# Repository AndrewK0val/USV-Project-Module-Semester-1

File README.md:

# USV-Project-Module-Semester-1
In this module I learned the process of electronic device design by creating a custom PCB board which will connect to a BBC Microbit module.
This custom board expands the existing feature-set of the BBC microbit by adding Wi-Fi networking and Bluetooth support, an LCD screen,
eight servo motor connections, audio output, and serial communication.

Autodesk Eagle was used to create the schematic and board design.

This is the finished schematic design:

Shown below is the complete board design:

Once the two designs were complete, gerber files were generated in Eagle and sent to a PCB manufacturer.
Depicted below is the printed PCB board:

This is the current iteration of the enclusure design to house the interface device. I have an obsession for automodive body design therefore
I wanted to incorporate a sports-car aesthetic to the housing of my custom board.
I plan to drill two holes on each side for each circular insert section to route cables for the 12v power and audio jack.
The design was created in Blender (free and open-source 3d-graphics and visual effects software)

This design will be 3D-printed in two parts (the main body and the lid) on an Ender 3 Pro 3D printer.

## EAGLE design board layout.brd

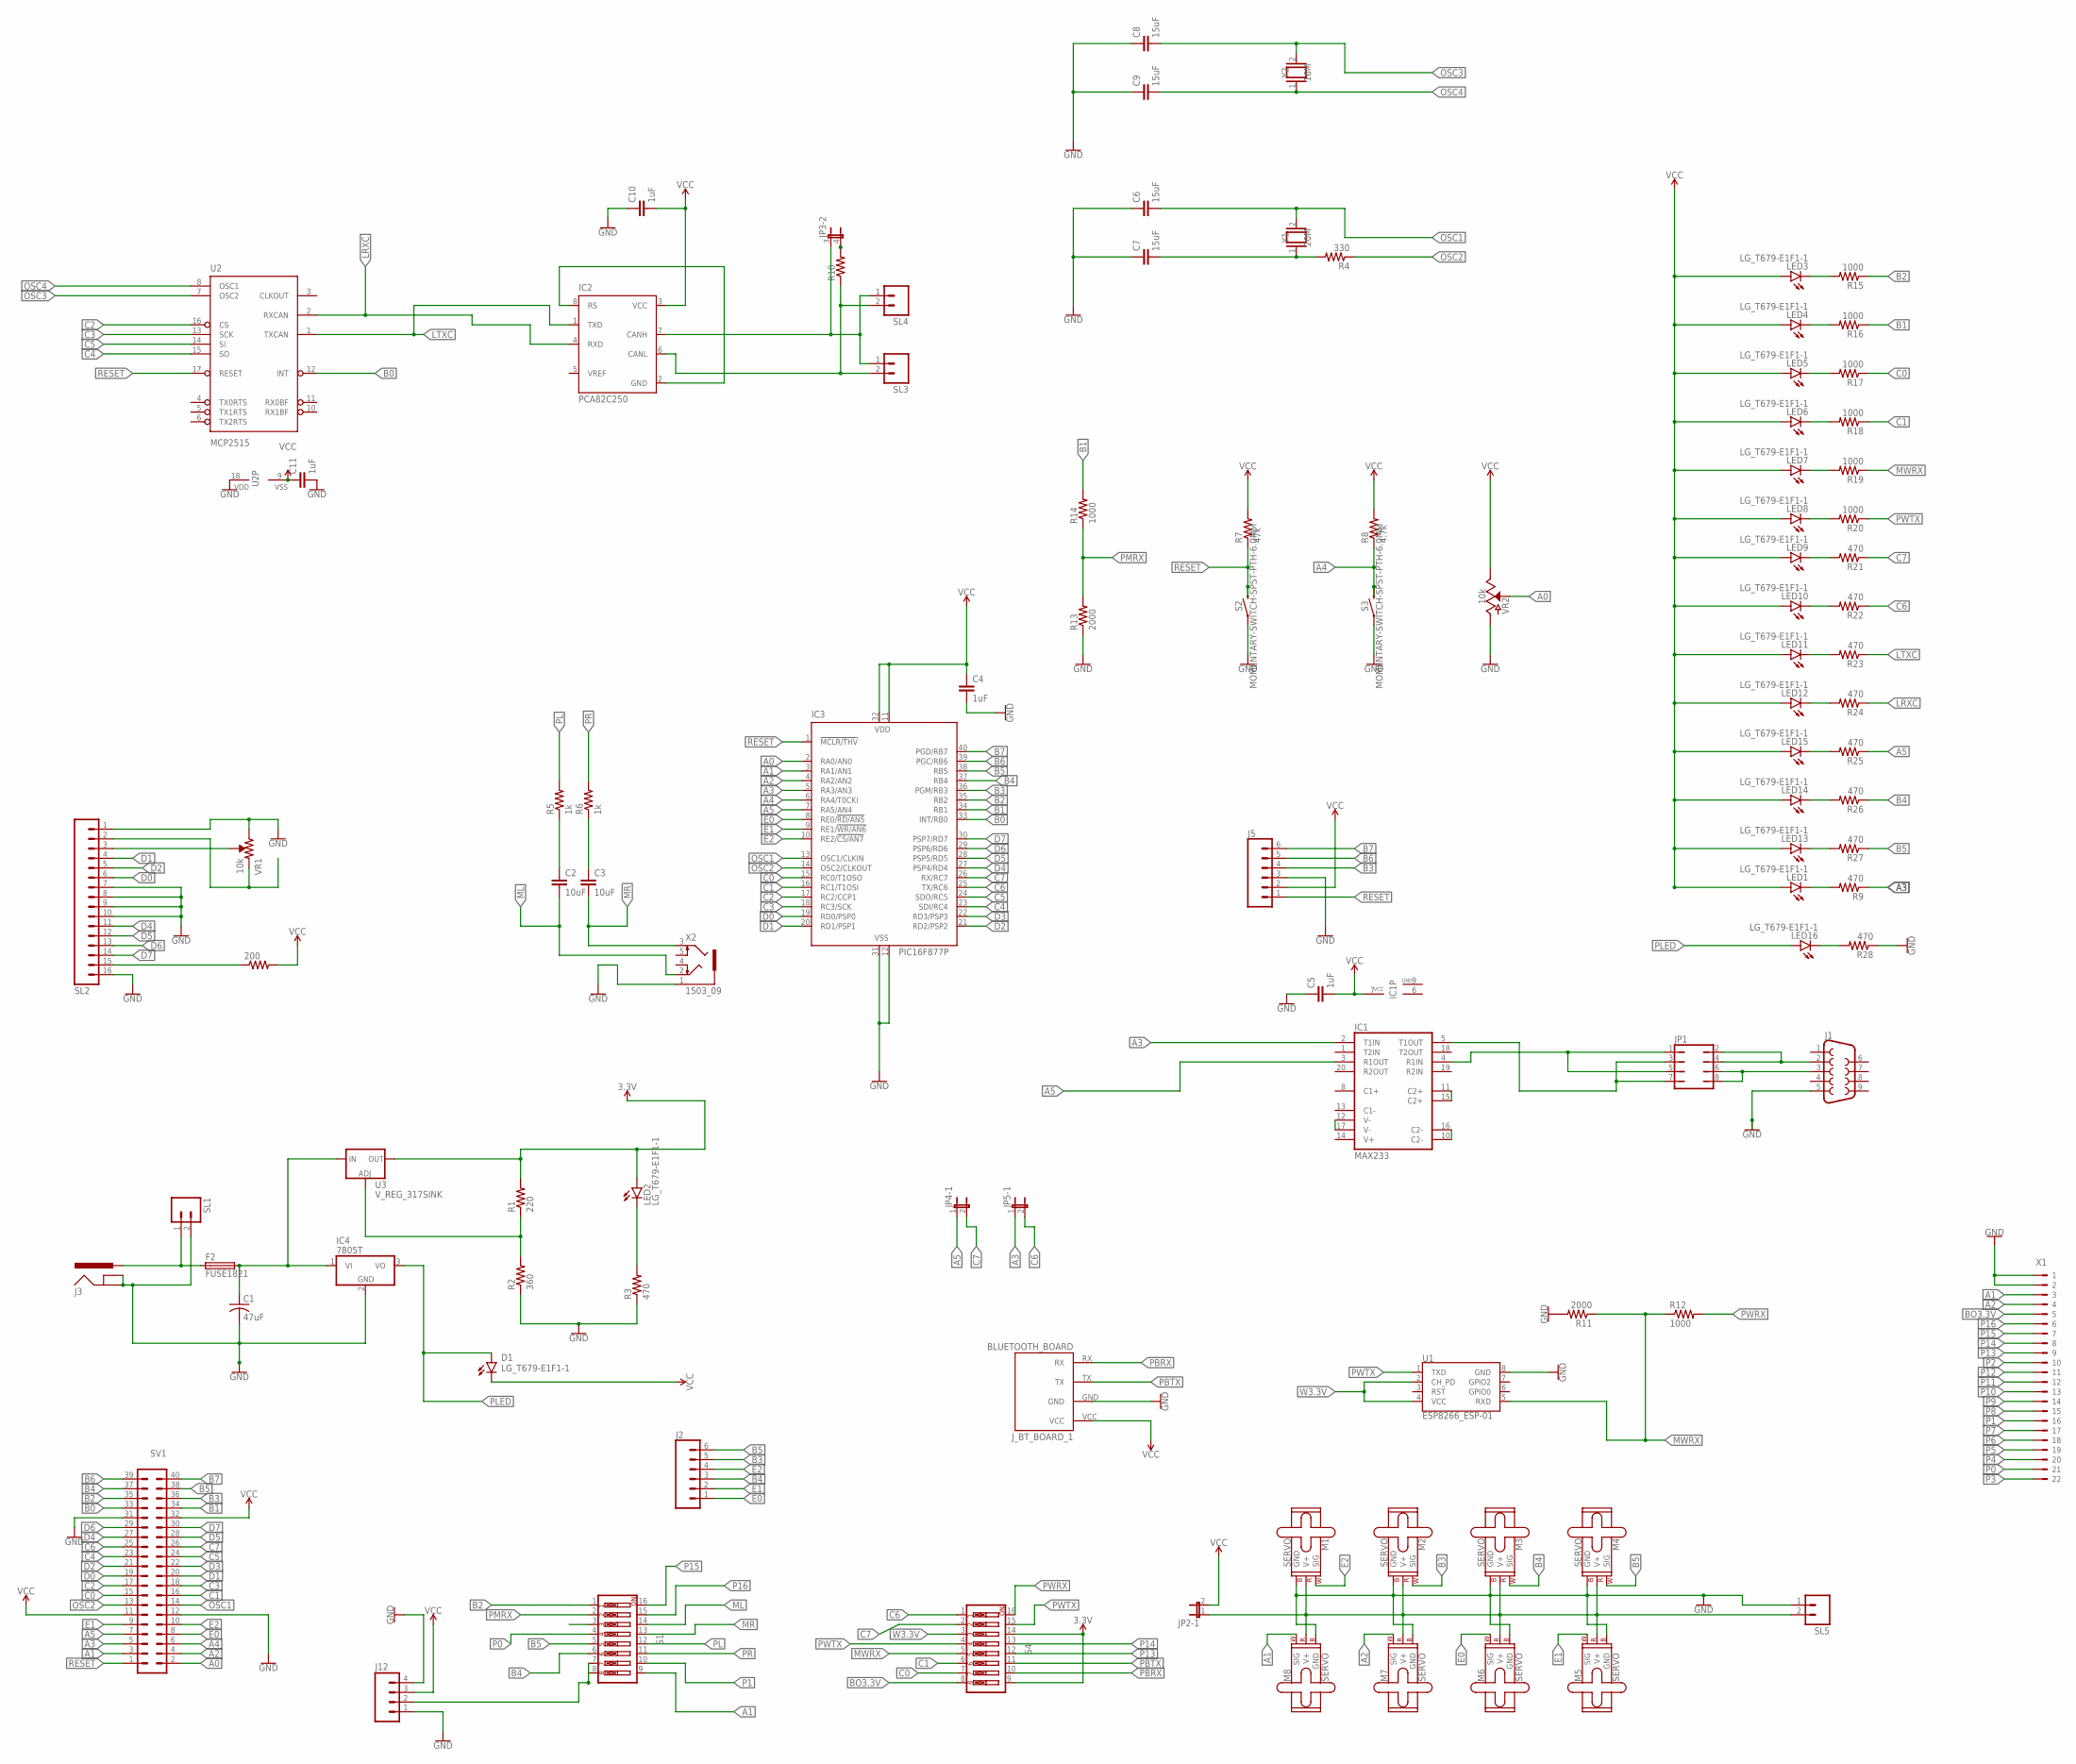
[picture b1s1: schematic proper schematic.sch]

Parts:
200: R-US_0204/5; 0204/5
C1: 47uF; C025-025X050
C2, C3: 10uF; C2.5-3
C4, C5, C10, C11: 1uF; C2.5-3
C6, C7, C8, C9: 15uF; C2.5-3
D1: LG_T679-E1F1-1; PLCC2
F2: FUSE1821; FUSE_HOLDER_MENTOR-1821
IC1: MAX233; DIL20
IC2: PCA82C250; DIL08
IC3: PIC16F877P; DIL40
IC4: 7805T; TO220H
J1: DB9FEMALE; DB9
J2, J5: CONN_062.5MM-6-90; 1X06_SCREW_TERMINAL_BLOCK
J3: POWER_JACK; POWER_JACK_PTH
J12: M04; 04P
JP1: JP4Q
JP2, JP3, JP4, JP5: JP2QE; JP2Q
J_BT_BOARD_1: BLUETOOTH_BOARD; BT_BOARD_FOOTPRINT
LED1, LED2, LED3, LED4, LED5, LED6, LED7, LED8, LED9, LED10, LED11, LED12, LED13, LED14, LED15, LED16: LG_T679-E1F1-1; PLCC2
M1, M2, M3, M4, M5, M6, M7, M8: SERVO; 1X03
R1: 220; 0204/5
R2: 360; 0204/5
R3, R9, R21, R22, R23, R24, R25, R26, R27, R28: 470; 0204/5
R4: 330; 0204/5
R5, R6: 1k; 0204/5
R7: 47k; 0204/5
R8: 4.7k; 0204/5
R10: R-US_0204/5; 0204/5
R11, R13: 2000; 0204/5
R12, R14, R15, R16, R17, R18, R19, R20: 1000; 0204/5
S1, S4: SW_DIP-8; EDG-08
S2, S3: MOMENTARY-SWITCH-SPST-PTH-6.0MM; TACTILE_SWITCH_PTH_6.0MM
SL1, SL3, SL4, SL5: M02; 02P
SL2: M16; 16P
SV1: MA20-2
U1: ESP8266_ESP-01
U2: MCP2515; DIP18
U3: V_REG_317SINK; TO220-ADJ
VR1: 10k; TRIMPOT-PTH-3386U
VR2: 10k; POT-PTH-ALPS
X1: 180G-22
X2: 1503_09
Y1: 20M; QS
Y2: 16M; QS

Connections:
3.3V: LED2.A, R1.2, S4.9, S4.14, U3.OUT
A0: IC3.2 (RA0/AN0), SV1.2, VR2.P$2 (S), VR2.P$3 (A)
A1: IC3.3 (RA1/AN1), M8.1 (SIG), S1.9, SV1.3, X1.3
A2: IC3.4 (RA2/AN2), M7.1 (SIG), SV1.4, X1.4
A3: IC1.2 (T1IN), IC3.5 (RA3/AN3), JP5.1, R9.1, SV1.5
A4: IC3.6 (RA4/T0CKI), R8.1, S3.3 (2), SV1.6
A5: IC1.3 (R1OUT), IC3.7 (RA5/AN4), JP4.1, R25.1, SV1.7
B0: IC3.33 (INT/RB0), SV1.33, U2.12 (INT)
B1: IC3.34 (RB1), R14.2, R16.1, SV1.34
B2: IC3.35 (RB2), R15.1, S1.1, SV1.35
B3: IC3.36 (PGM/RB3), J2.5, J5.4, M2.1 (SIG), SV1.36
B4: IC3.37 (RB4), J2.3, M3.1 (SIG), R26.1, S1.6, SV1.37
B5: IC3.38 (RB5), J2.6, M4.1 (SIG), R27.1, S1.5, SV1.38
B6: IC3.39 (PGC/RB6), J5.5, SV1.39
B7: IC3.40 (PGD/RB7), J5.6, SV1.40
BO3.3V: S4.8, X1.5
C0: IC3.15 (RC0/T1OSO), R17.1, S4.7, SV1.15
C1: IC3.16 (RC1/T1OSI), R18.1, S4.6, SV1.16
C2: IC3.17 (RC2/CCP1), SV1.17, U2.16 (CS)
C3: IC3.18 (RC3/SCK), SV1.18, U2.13 (SCK)
C4: IC3.23 (SDI/RC4), SV1.23, U2.15 (SO)
C5: IC3.24 (SDO/RC5), SV1.24, U2.14 (SI)
C6: IC3.25 (TX/RC6), JP5.2, R22.1, S4.1, SV1.25
C7: IC3.26 (RX/RC7), JP4.2, R21.1, S4.2, SV1.26
D0: IC3.19 (RD0/PSP0), SL2.6, SV1.19
D1: IC3.20 (RD1/PSP1), SL2.4, SV1.20
D2: IC3.21 (RD2/PSP2), SL2.5, SV1.21
D3: IC3.22 (RD3/PSP3), SV1.22
D4: IC3.27 (PSP4/RD4), SL2.11, SV1.27
D5: IC3.28 (PSP5/RD5), SL2.12, SV1.28
D6: IC3.29 (PSP6/RD6), SL2.13, SV1.29
D7: IC3.30 (PSP7/RD7), SL2.14, SV1.30
E0: IC3.8 (RE0/!RD/AN5), J2.1, M6.1 (SIG), SV1.8
E1: IC3.9 (RE1/!WR/AN6), J2.2, M5.1 (SIG), SV1.9
E2: IC3.10 (RE2/!CS/AN7), J2.4, M1.1 (SIG), SV1.10
GND: C1.2, C4.2, C5.1, C6.1, C7.1, C8.1, C9.1, C10.1, C11.2, IC1.6 (GND), IC1.9 (GND), IC3.12 (VSS), IC3.31 (VSS), IC4.2 (GND), J1.5, J3.GND, J3.GNDBREAK, J5.3, J12.1, J12.4, J_BT_BOARD_1.GND, M1.3 (GND), M2.3 (GND), M3.3 (GND), M4.3 (GND), M5.3 (GND), M6.3 (GND), M7.3 (GND), M8.3 (GND), R2.1, R3.1, R11.2, R13.1, R28.1, S2.1, S3.1, SL1.2, SL2.1, SL2.7, SL2.8, SL2.9, SL2.10, SL2.16, SL5.1, SV1.12, SV1.31, U1.8 (GND), U2.18 (VDD), VR1.3 (CW), X1.1, X1.2, X2.1
LRXC: IC2.4 (RXD), R24.1, U2.2 (RXCAN)
LTXC: IC2.1 (TXD), R23.1, U2.1 (TXCAN)
ML: C2.2, S1.14, X2.2
MR: C3.2, S1.13, X2.3
MWRX: R11.1, R12.1, R19.1, S4.5, U1.5 (RXD)
unnamed: LED1.C, R9.2
unnamed: JP3.4 (2), R10.2
unnamed: IC1.10 (C2-), IC1.16 (C2-)
unnamed: C1.1, F2.B (2), IC4.1 (VI), U3.IN
unnamed: F2.A (1), J3.PWR, SL1.1
unnamed: R1.1, R2.2, U3.ADJ
unnamed: LED2.C, R3.2
unnamed: IC1.5 (T1OUT), JP1.3, JP1.7
unnamed: IC1.4 (R1IN), JP1.1, JP1.5
unnamed: J1.3, JP1.6, JP1.8
unnamed: J1.2, JP1.2, JP1.4
unnamed: C2.1, R5.1
unnamed: IC1.12 (V-), IC1.17 (V-)
unnamed: IC1.11 (C2+), IC1.15 (C2+)
unnamed: C3.1, R6.1
unnamed: 200.1, SL2.15
unnamed: C7.2, R4.2, Y1.1
unnamed: SL2.3, VR1.2 (WIPER)
unnamed: SL2.2, VR1.1 (CCW)
unnamed: JP2.1, M1.2 (V+), M2.2 (V+), M3.2 (V+), M4.2 (V+), M5.2 (V+), M6.2 (V+), M7.2 (V+), M8.2 (V+), SL5.2
unnamed: J12.2, S1.7, S1.8
unnamed: IC2.2 (GND), IC2.8 (RS)
unnamed: IC2.6 (CANL), R10.1, SL3.2, SL4.2
unnamed: IC2.7 (CANH), JP3.3 (1), SL3.1, SL4.1
unnamed: LED3.C, R15.2
unnamed: LED4.C, R16.2
unnamed: LED5.C, R17.2
unnamed: LED6.C, R18.2
unnamed: LED7.C, R19.2
unnamed: LED8.C, R20.2
unnamed: LED9.C, R21.2
unnamed: LED10.C, R22.2
unnamed: LED11.C, R23.2
unnamed: LED12.C, R24.2
unnamed: LED15.C, R25.2
unnamed: LED14.C, R26.2
unnamed: LED13.C, R27.2
unnamed: LED16.C, R28.2
OSC1: C6.2, IC3.13 (OSC1/CLKIN), SV1.14, Y1.2
OSC2: IC3.14 (OSC2/CLKOUT), R4.1, SV1.13
OSC3: C8.2, U2.7 (OSC2), Y2.2
OSC4: C9.2, U2.8 (OSC1), Y2.1
P0: S1.4, X1.21
P1: S1.10, X1.16
P2: X1.10
P3: X1.22
P4: X1.20
P5: X1.19
P6: X1.18
P7: X1.17
P8: X1.15
P9: X1.14
P10: X1.13
P11: X1.12
P12: X1.11
P13: S4.12, X1.9
P14: S4.13, X1.8
P15: S1.16, X1.7
P16: S1.15, X1.6
PBRX: J_BT_BOARD_1.RX, S4.10
PBTX: J_BT_BOARD_1.TX, S4.11
PL: R5.2, S1.12
PLED: D1.A, IC4.3 (VO), LED16.A
PMRX: R13.2, R14.1, S1.2
PR: R6.2, S1.11
PWRX: R12.2, S4.16
PWTX: R20.1, S4.4, S4.15, U1.1 (TXD)
RESET: IC3.1 (!MCLR/THV), J5.1, R7.1, S2.3 (2), SV1.1, U2.17 (RESET)
VCCA: 200.2, C4.1, C5.2, C10.2, C11.1, D1.C, IC1.7 (VCC), IC2.3 (VCC), IC3.11 (VDD), IC3.32 (VDD), J5.2, J12.3, JP2.2, J_BT_BOARD_1.VCC, LED1.A, LED3.A, LED4.A, LED5.A, LED6.A, LED7.A, LED8.A, LED9.A, LED10.A, LED11.A, LED12.A, LED13.A, LED14.A, LED15.A, R7.2, R8.2, SV1.11, SV1.32, U2.9 (VSS), VR2.P$1 (E)
W3.3V: S4.3, U1.2 (CH_PD), U1.4 (VCC)

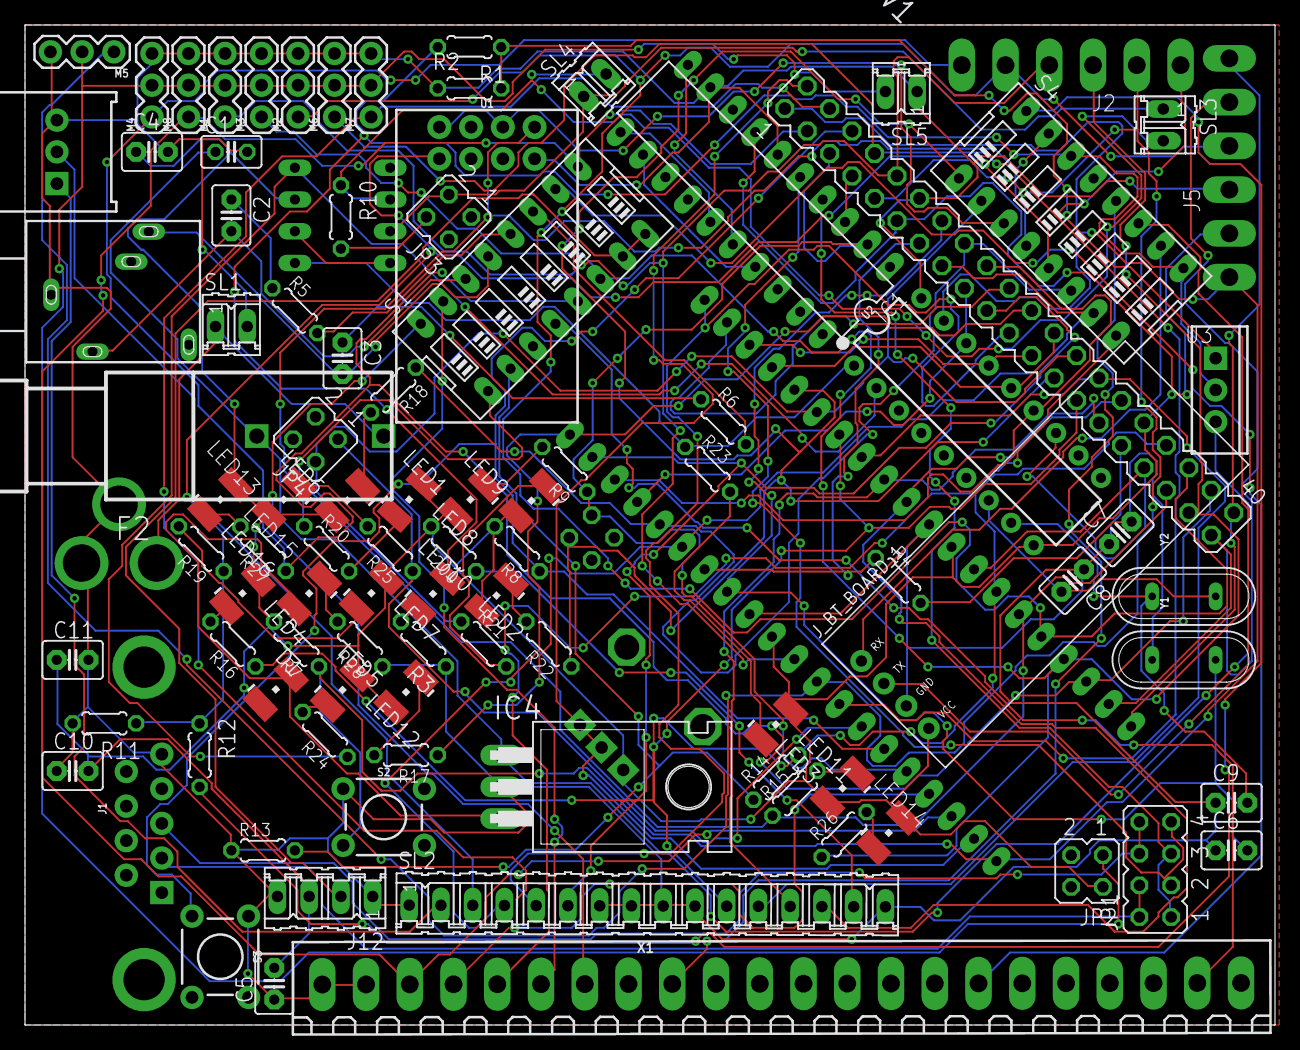
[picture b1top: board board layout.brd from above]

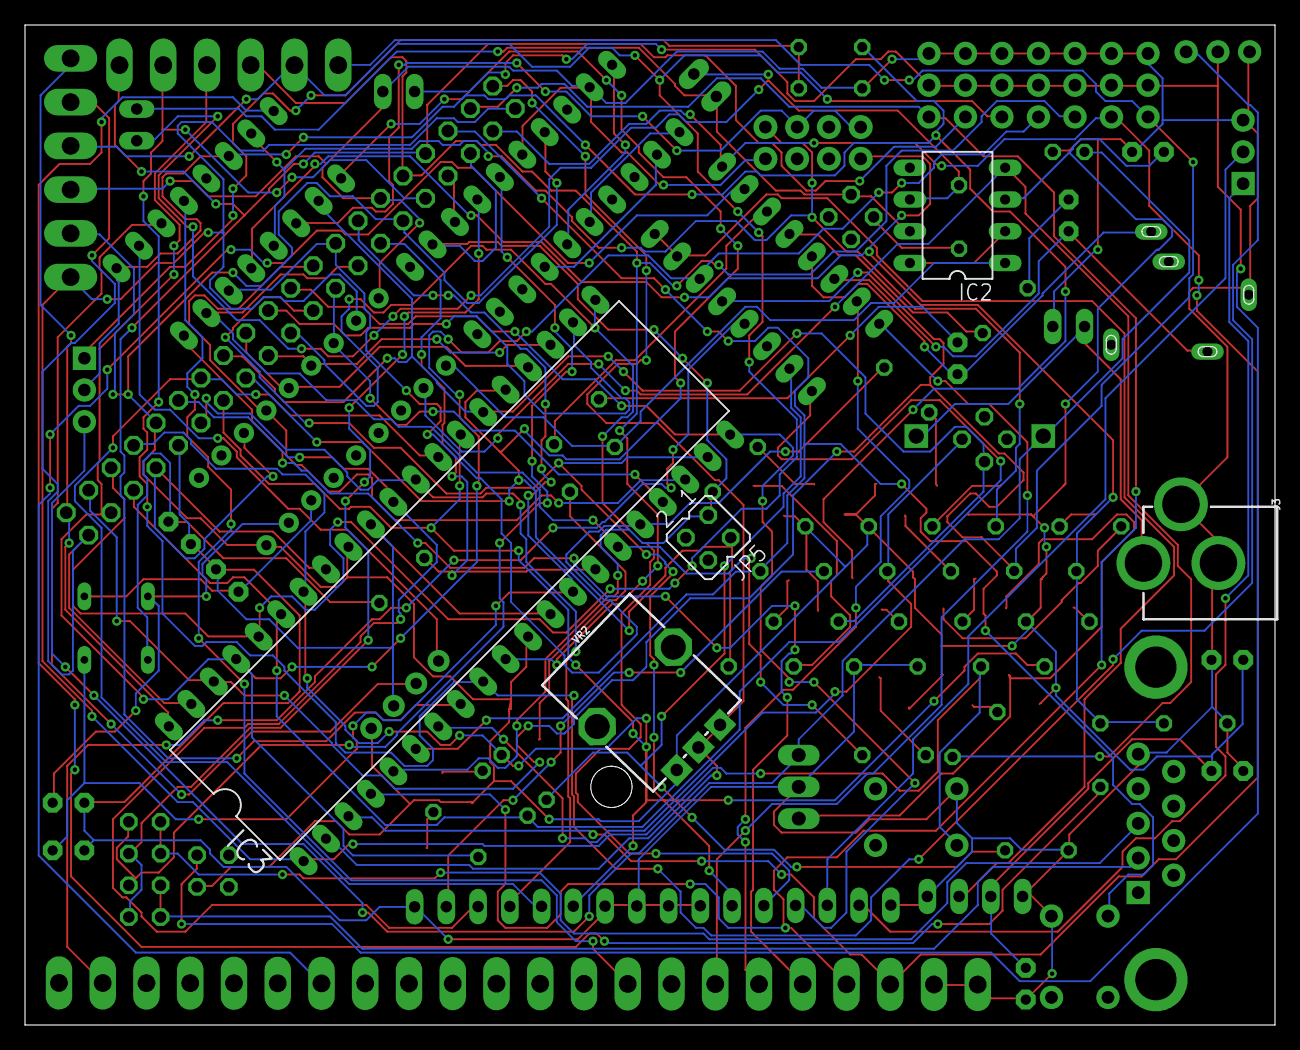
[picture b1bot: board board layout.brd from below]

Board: 2 copper layers, 100.0 x 80.0 mm, 100 parts (5 on the bottom side), 100 nets.

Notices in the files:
parts and their libraries:
SparkFun-Connectors: Licensing: Creative Commons ShareAlike 4.0 International - https://creativecommons.org/licenses/by-sa/4.0
